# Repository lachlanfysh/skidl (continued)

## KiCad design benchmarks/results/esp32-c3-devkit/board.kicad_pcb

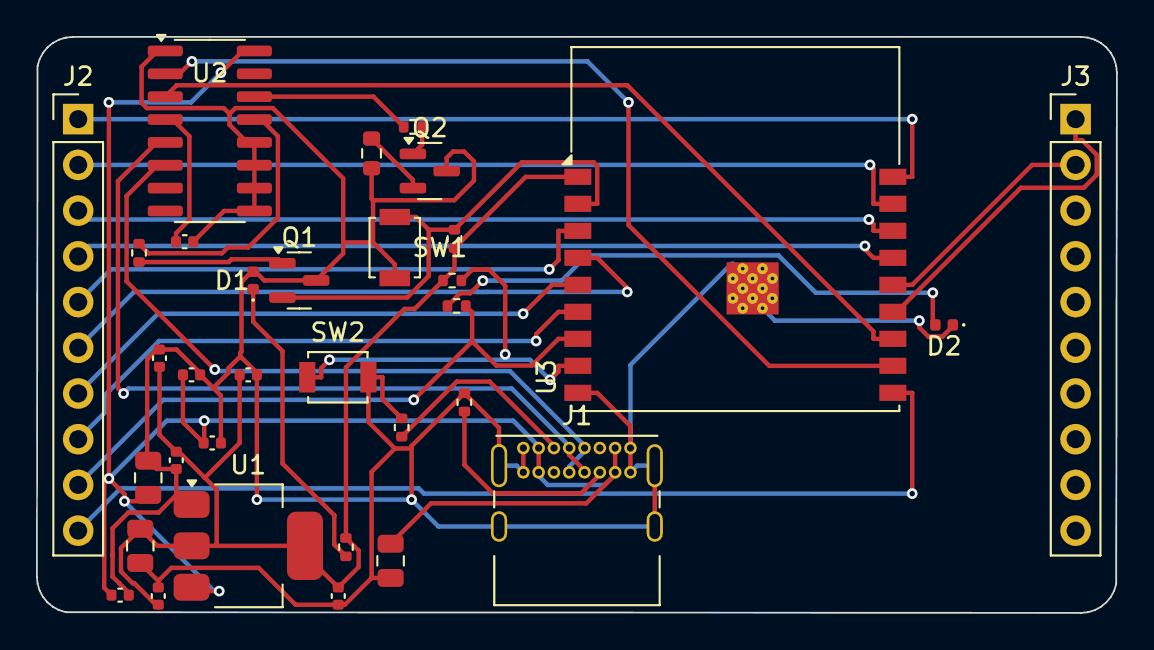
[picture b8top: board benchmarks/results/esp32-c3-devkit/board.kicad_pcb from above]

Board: 2 copper layers, 60.0 x 32.0 mm, 33 parts (0 on the bottom side), 30 nets.

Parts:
C1, C4, C6, C7, C8, C9, C10, C11, C12: 100nF; C_0402_1005Metric
C2, C3, C5: 10uF; C_0805_2012Metric
D1, D2: LED; LED_0402_1005Metric
J1: USB_C_Receptacle_USB2.0_14P; USB_C_Receptacle_GCT_USB4085
J2, J3: Conn_01x10; PinHeader_1x10_P2.54mm_Vertical
Q1, Q2: Q_NPN_BCE; SOT-23
R1, R2: 5.1k; R_0402_1005Metric
R3, R4, R5, R6: 10k; R_0402_1005Metric
R7: 1k; R_0402_1005Metric
R8: 330R; R_0402_1005Metric
R9: 10K; R_0603_1608Metric
SW1, SW2: SW_Push; SW_SPST_B3U-1000P
U1: AMS1117-3.3; SOT-223-3_TabPin2
U2: CH340C; SOIC-16_3.9x9.9mm_P1.27mm
U3: ESP32-C3-WROOM-02

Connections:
BOOT: Q2.2, R6.2, R9.1, SW2.1, U3.8
DTR_N: R3.1, U2.13
GND: C1.2, C2.2, C3.2, C4.2, C5.2, C6.2, C7.2, C8.2, C9.2, C10.2, C11.2, C12.2, D1.2, D2.1, J1.A1, J1.A12, J1.B1, J1.B12, J1.S1, Q1.3, Q2.3, R1.2, R2.2, R9.2, SW1.2, SW2.2, U1.1, U2.1, U2.9, U2.10, U2.11, U2.12, U3.9, U3.19
IO0: J2.1, U3.18
IO1: J2.2, U3.17
IO2: J2.3, U3.16
IO3: J2.4, U3.15
IO4: J2.5, U3.3
IO5: J2.6, U3.4
IO6: J2.7, U3.5
IO7: J2.8, U3.6
IO8: J2.9, R8.1, U3.7
IO10: J2.10, U3.10
IO18: J3.1, U3.13
IO19: J3.2, U3.14
unnamed: J1.A5, R1.1
unnamed: J1.B5, R2.1
unnamed: C7.1, U2.4
unnamed: Q1.1, R3.2
unnamed: Q2.1, R4.2
unnamed: D1.1, R7.2
unnamed: D2.2, R8.2
RST_N: Q1.2, R5.2, SW1.1, U3.2
RTS_N: R4.1, U2.14
UART_RX: U2.3, U3.12
UART_TX: U2.2, U3.11
USB_DM: J1.A7, J1.B7, U2.6
USB_DP: J1.A6, J1.B6, U2.5
VBUS: C1.1, C2.1, C3.1, C4.1, C8.1, J1.A4, J1.A9, J1.B4, J1.B9, U1.3, U2.16
VCC3V3: C5.1, C6.1, C9.1, C10.1, C11.1, C12.1, R5.1, R6.1, R7.1, U1.2, U3.1

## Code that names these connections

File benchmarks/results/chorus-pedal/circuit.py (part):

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# ---- Clock nets ----
cp1  = Net("CP1")
cp2  = Net("CP2")
vgg  = Net("VGG")     # MN3101 VGG_OUT -> MN3007 VGG pin

# ---- Audio signal nets ----
audio_in    = Net("AUDIO_IN")    # tip of input jack (post true-bypass pole)
audio_out   = Net("AUDIO_OUT")   # tip of output jack (post true-bypass pole)
circuit_in  = Net("CIRCUIT_IN")  # effect input (from bypass switch pole A)
buf_out     = Net("BUF_OUT")     # TL072A buffered output
bbd_in      = Net("BBD_IN")      # after LP filter, into MN3007 IN pin
bbd_out     = Net("BBD_OUT")     # MN3007 OUT2, after LP filter
depth_wip   = Net("DEPTH_WIP")   # depth pot wiper (wet level to mixer)
circuit_out = Net("CIRCUIT_OUT") # TL072B mixed output (effect output to bypass switch)
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    gnd       += j_out["S"]

    # DPDT true bypass footswitch
    # Pole1 (pins 1,2,3): A(1)=circuit_in, B(2)=audio_in, C(3)=audio_out (bypass path)
    # Pole2 (pins 4,5,6): A(4)=audio_out, B(5)=circuit_out, C(6)=NC
    fsw = Part("Switch", "SW_DPDT_x2",
               footprint="Button_Switch_THT:SW_PUSH_E-Switch_FS5700DP_DPDT")
    fsw.edge_preference = "bottom"
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
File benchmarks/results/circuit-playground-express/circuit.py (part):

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    c_core[2] += gnd

    # USB
    mcu["PA24"] += usb_dm   # D-
    mcu["PA25"] += usb_dp   # D+

    # SWD / RESET
    mcu["~{RESET}"] += reset_n
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    mcu["PA06"] += neopixel

    # IR TX: PA02 (TCCx/WO for carrier)
    mcu["PA02"] += ir_tx
    # IR RX: PA03
    mcu["PA03"] += ir_rx

    # Buttons - active low with pull-up
    mcu["PA04"] += btn_a
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    # Slide switch
    mcu["PA07"] += slide_sw

    # Speaker: PA02 is IR_TX (PWM modulated). Audio out uses PA00 (DAC on SAMD21).
    # CPX uses class-D via PA02, but we separate concerns: use PA12 for speaker
    mcu["PA12"] += speaker

    # Speaker enable
    mcu["PA14"] += spk_en
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
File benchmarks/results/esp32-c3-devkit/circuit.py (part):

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ldo_3v3(vbus, vcc33, gnd)
ch340c_bridge(vbus, usb_dp, usb_dm, uart_tx, uart_rx, dtr_n, rts_n, gnd)
auto_reset(vcc33, dtr_n, rts_n, rst_n, boot, gnd)
esp32c3(vcc33, gnd, uart_rx, uart_tx, rst_n, boot, gpio_a, gpio_b_nets)
buttons(rst_n, boot, gnd)
leds(vcc33, led_gpio, gnd)
gpio_headers(gpio_a, gpio_b_nets, vcc33, gnd)
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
